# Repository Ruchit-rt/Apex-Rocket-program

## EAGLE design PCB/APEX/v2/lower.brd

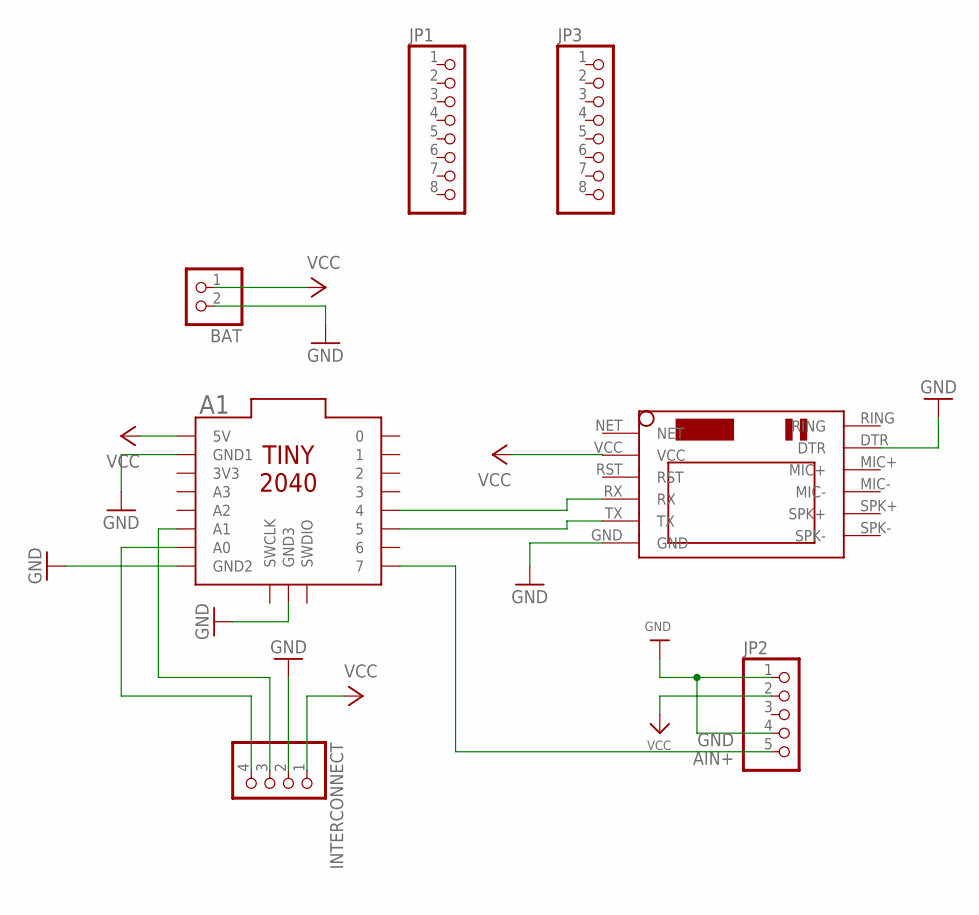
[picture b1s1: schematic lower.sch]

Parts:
A1: TINY2040
BAT: JST_2PIN-THM-RA; JST-PH-2-THM-RA
INTERCONNECT: PINHD-1X4; 1X04
JP1, JP3: PINHD-1X8; 1X08
JP2: HEADER-1X570MIL; 1X05_ROUND_70
U$2: SIM800LMODULE

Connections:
AIN+: A1.7, JP2.5
GND: A1.GND1, A1.GND2, A1.GND3, BAT.2 (1), INTERCONNECT.2, JP2.1, JP2.4, U$2.DTR, U$2.GND
unnamed: A1.4, U$2.RX
unnamed: A1.5, U$2.TX
unnamed: A1.A1, INTERCONNECT.3
unnamed: A1.A0, INTERCONNECT.4
VCC: A1.5V, BAT.1 (2), INTERCONNECT.1, JP2.2, U$2.VCC

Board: 2 copper layers, 7 parts (0 on the bottom side), 7 nets, no tracks yet.

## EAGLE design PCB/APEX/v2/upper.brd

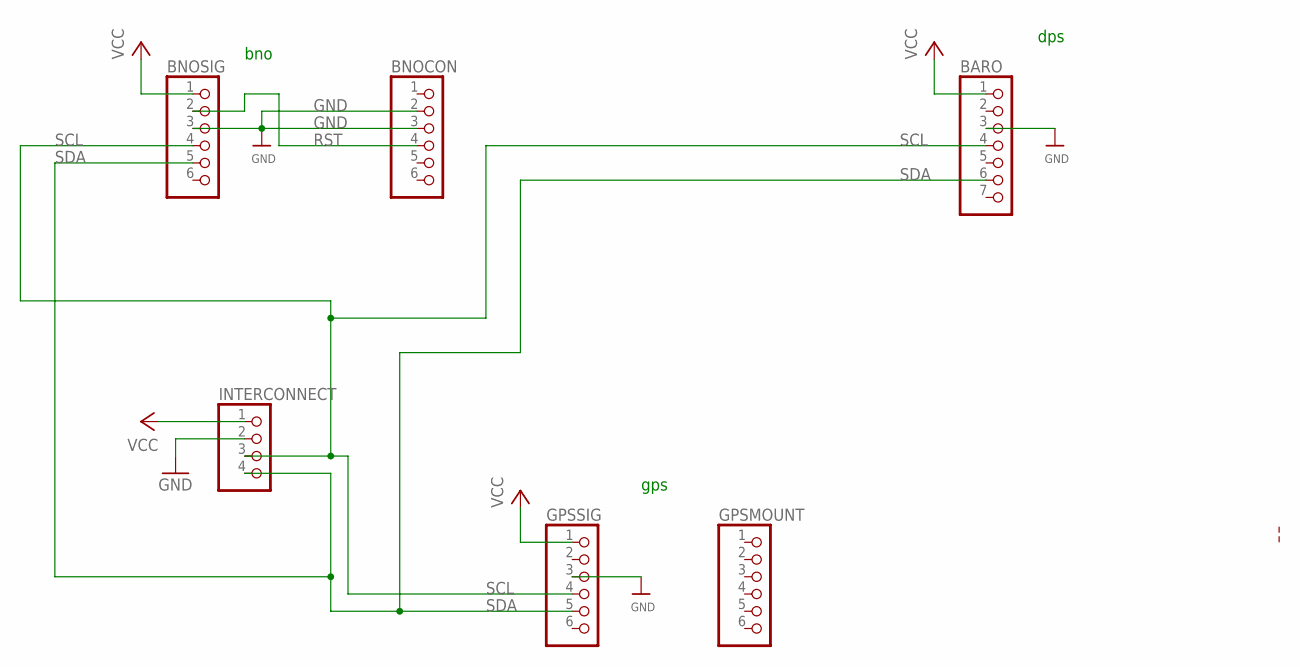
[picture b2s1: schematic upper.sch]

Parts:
BARO: HEADER-1X770MIL; 1X07_ROUND_70
BNOCON: HEADER-1X670MIL; 1X06_ROUND_70
BNOSIG: HEADER-1X670MIL; 1X06_ROUND_70
GPSMOUNT: HEADER-1X670MIL; 1X06_ROUND_70
GPSSIG: HEADER-1X670MIL; 1X06_ROUND_70
INTERCONNECT: PINHD-1X4; 1X04

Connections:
GND: BARO.3, BNOCON.2, BNOCON.3, BNOSIG.3, GPSSIG.3, INTERCONNECT.2
RST: BNOCON.4, BNOSIG.2
SCL: BARO.4, BNOSIG.4, GPSSIG.4, INTERCONNECT.3
SDA: BARO.6, BNOSIG.5, GPSSIG.5, INTERCONNECT.4
VCC: BARO.1, BNOSIG.1, GPSSIG.1, INTERCONNECT.1

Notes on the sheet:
bno
dps
gps

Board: 2 copper layers, 6 parts (0 on the bottom side), 5 nets, no tracks yet.

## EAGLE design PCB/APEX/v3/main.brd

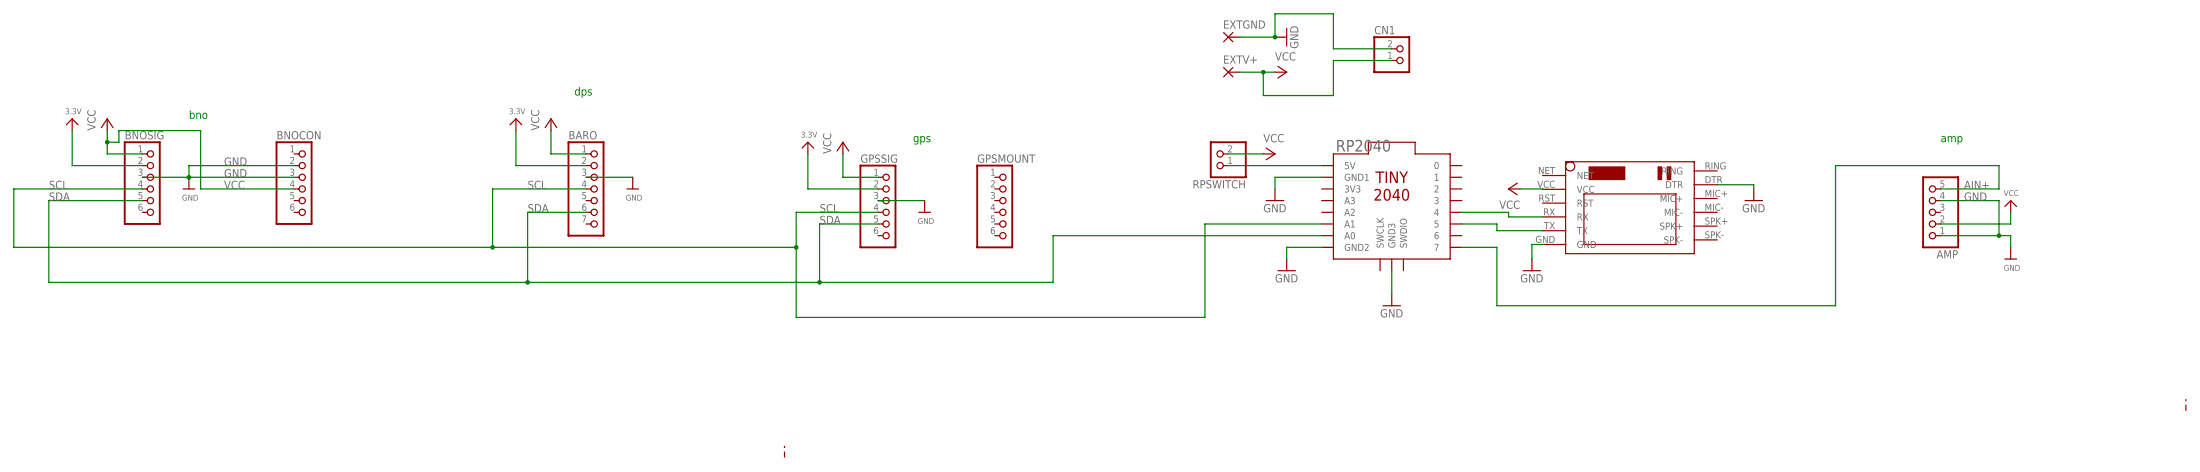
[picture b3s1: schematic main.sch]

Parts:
AMP: HEADER-1X570MIL; 1X05_ROUND_70
BARO: HEADER-1X770MIL; 1X07_ROUND_70
BNOCON: HEADER-1X670MIL; 1X06_ROUND_70
BNOSIG: HEADER-1X670MIL; 1X06_ROUND_70
CN1: JST_2PIN-THM-RA; JST-PH-2-THM-RA
EXTGND: SMD5; SMD2,54-5,08
EXTV+: SMD5; SMD2,54-5,08
GPSMOUNT: HEADER-1X670MIL; 1X06_ROUND_70
GPSSIG: HEADER-1X670MIL; 1X06_ROUND_70
RP2040: TINY2040
RPSWITCH: PINHD-1X2; 1X02
U$1: SIM800LMODULE

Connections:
3.3V: BARO.2, BNOSIG.2, GPSSIG.2
AIN+: AMP.5, RP2040.7
GND: AMP.1, AMP.4, BARO.3, BNOCON.2, BNOCON.3, BNOSIG.3, CN1.2 (1), EXTGND.1, GPSSIG.3, RP2040.GND1, RP2040.GND2, RP2040.GND3, U$1.DTR, U$1.GND
unnamed: RP2040.4, U$1.RX
unnamed: RP2040.5, U$1.TX
unnamed: RP2040.5V, RPSWITCH.1
SCL: BARO.4, BNOSIG.4, GPSSIG.4, RP2040.A1
SDA: BARO.6, BNOSIG.5, GPSSIG.5, RP2040.A0
VCC: AMP.2, BARO.1, BNOCON.4, BNOSIG.1, CN1.1 (2), EXTV+.1, GPSSIG.1, RPSWITCH.2, U$1.VCC

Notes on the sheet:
bno
dps
gps
amp

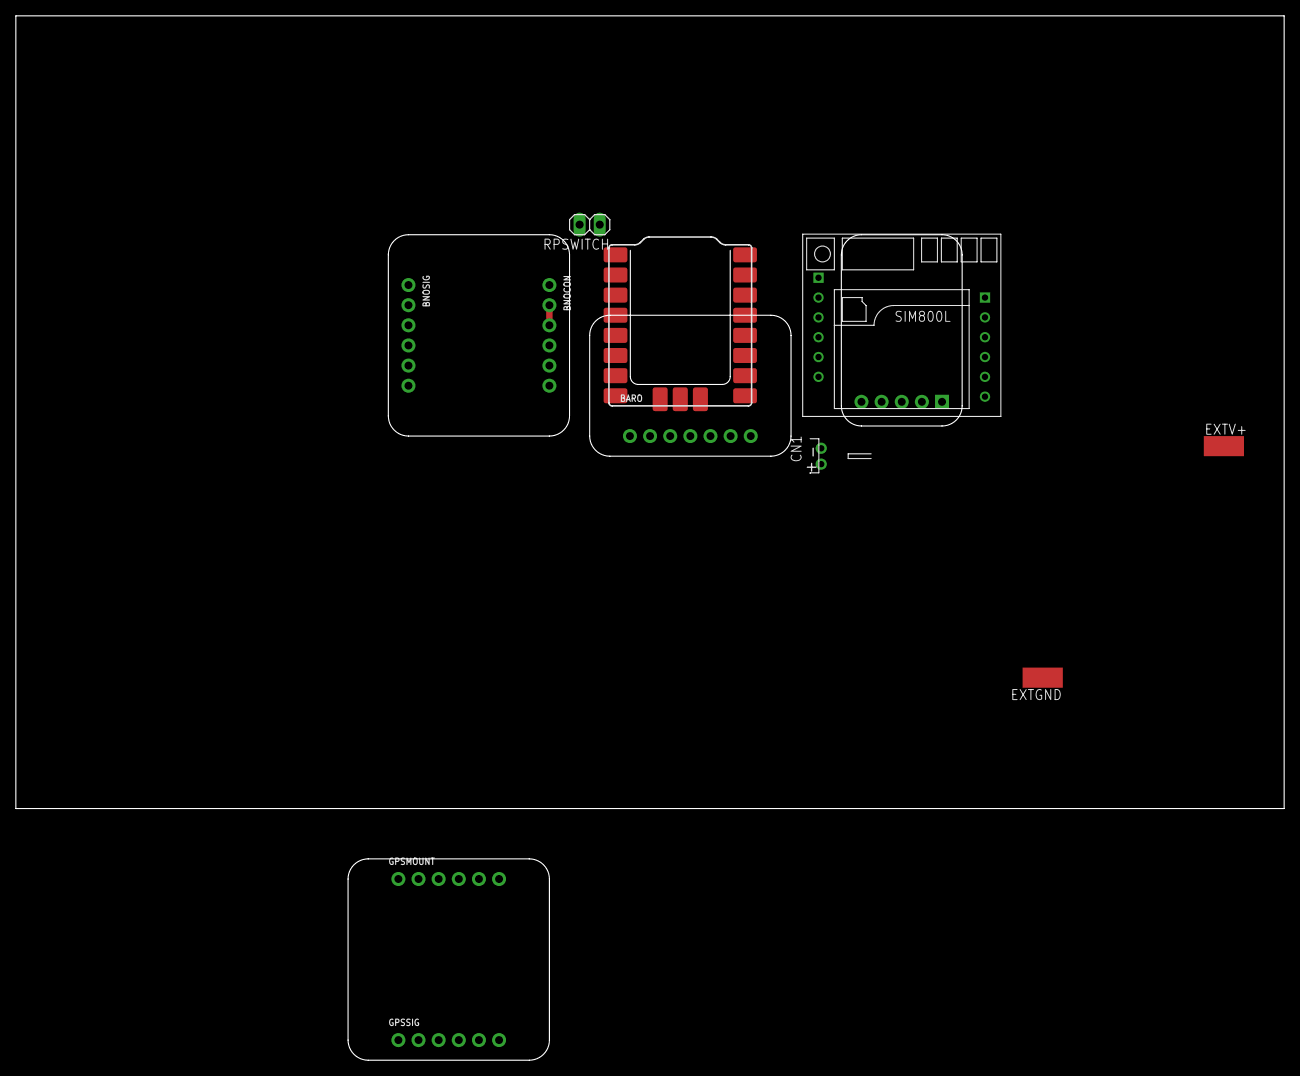
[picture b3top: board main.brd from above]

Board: 2 copper layers, 160.0 x 100.0 mm, 12 parts (0 on the bottom side), 9 nets.

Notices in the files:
parts and their libraries:
microbuilder: This work is placed in the public domain, and may be freely used for commercial and non-commercial work with the following conditions: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
